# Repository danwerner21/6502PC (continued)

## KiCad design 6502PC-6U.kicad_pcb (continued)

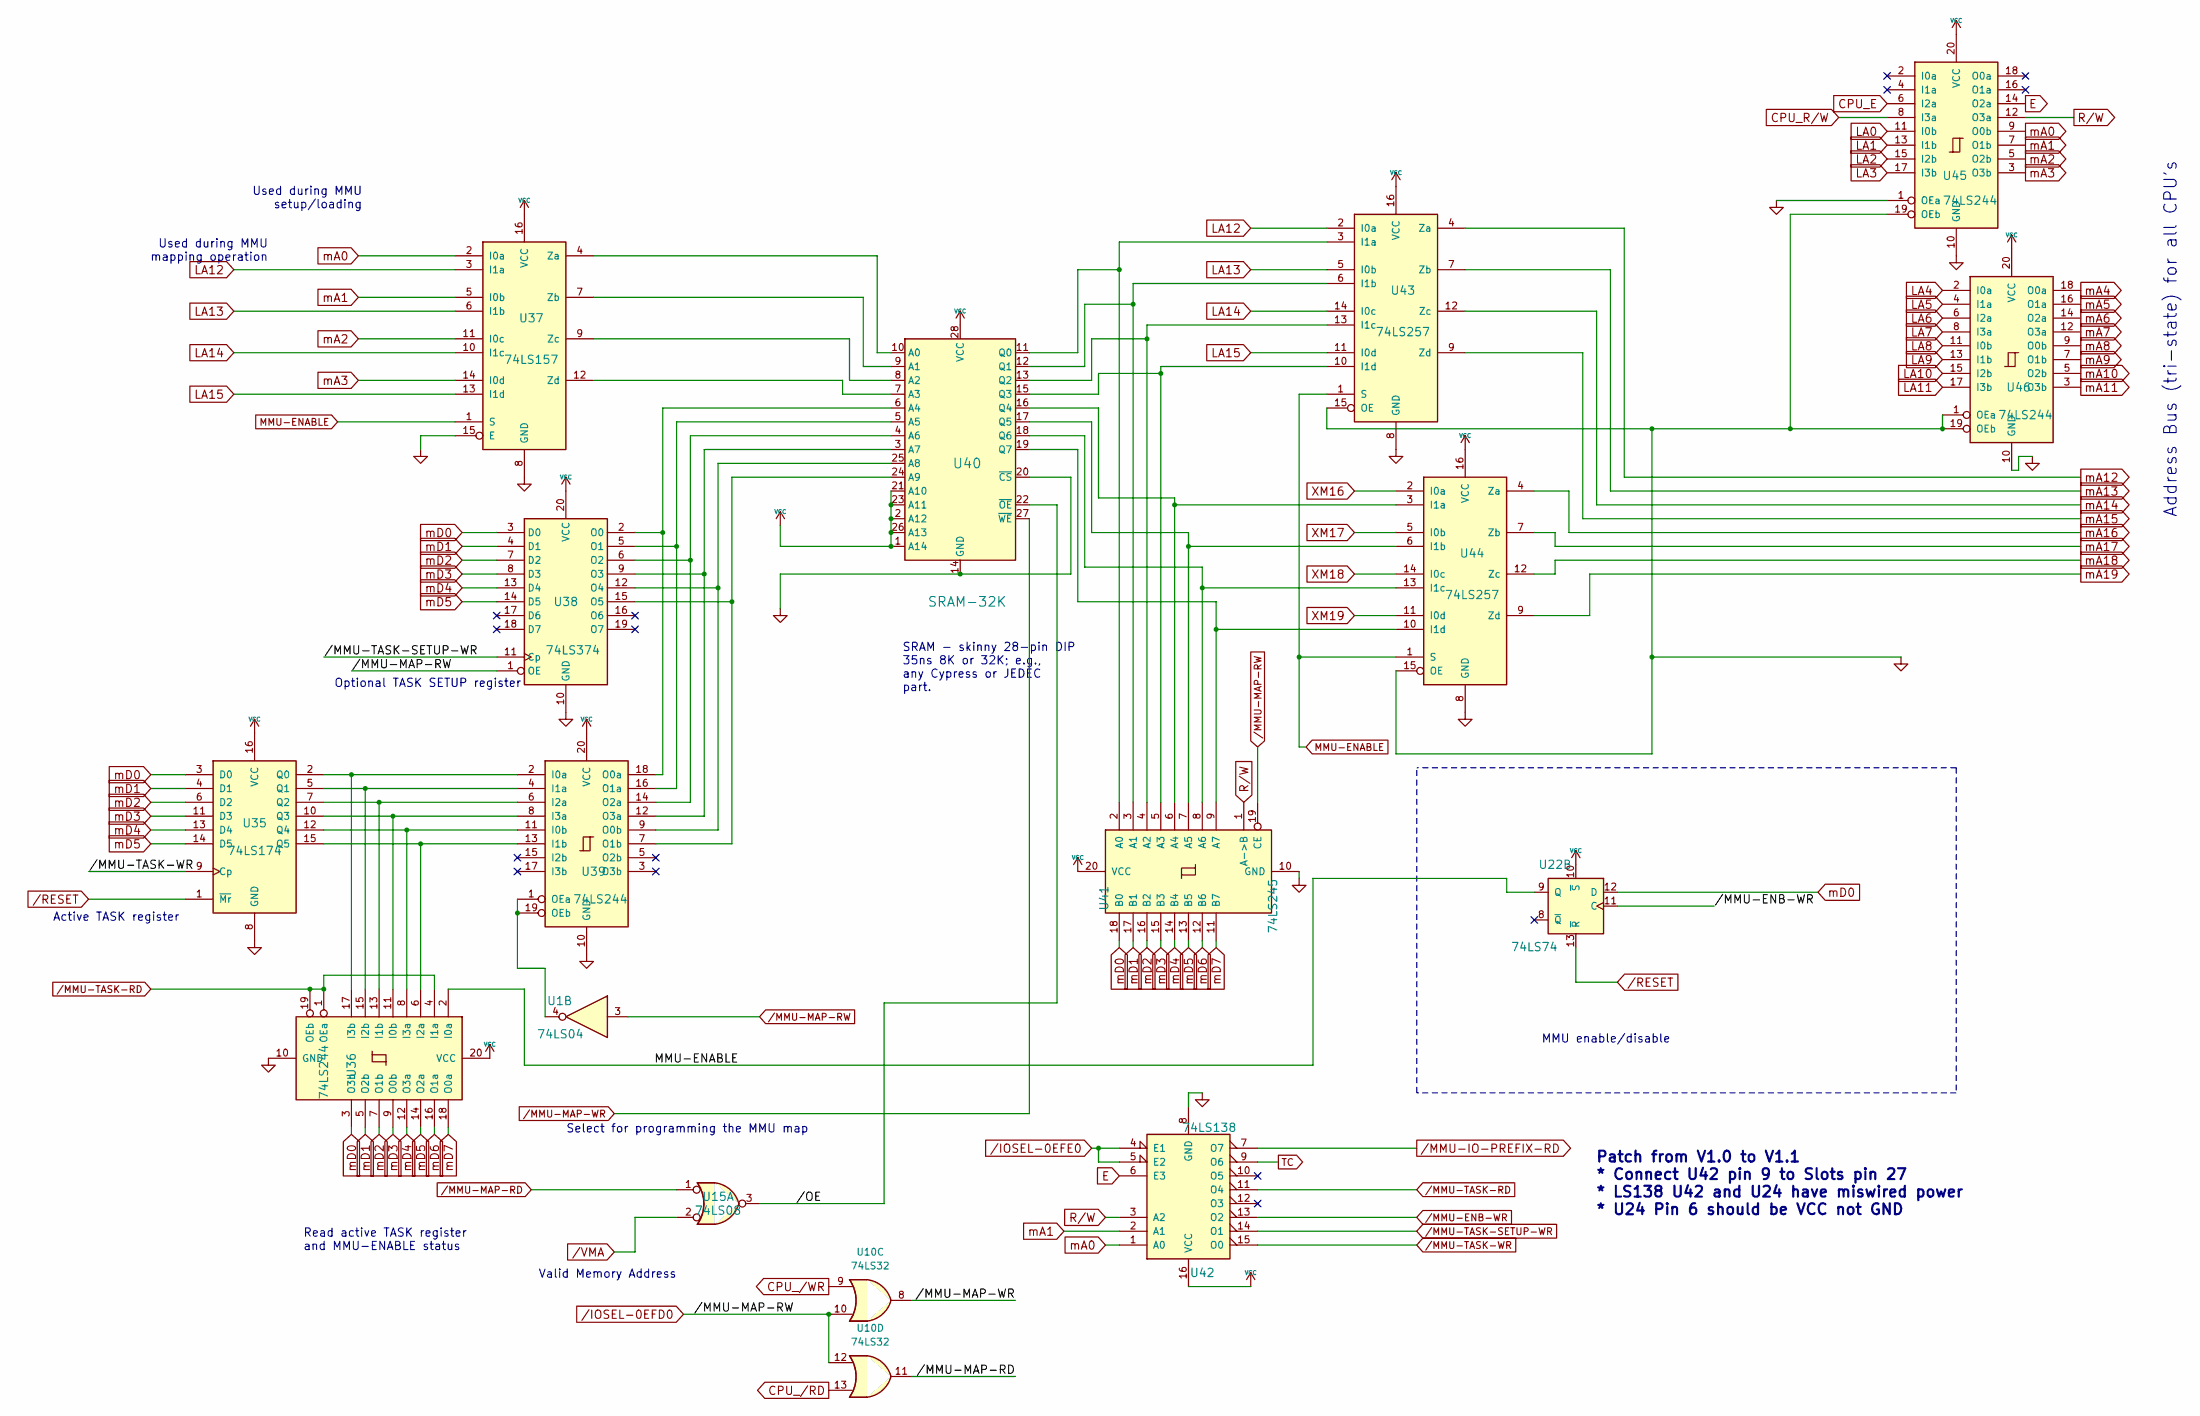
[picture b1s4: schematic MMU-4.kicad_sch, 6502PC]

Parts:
U1: 74LS04; STD_DDW_DIP14
U10: 74LS32; STD_DDW_DIP14
U15: 74LS08; STD_DDW_DIP14
U22: 74LS74; STD_DDW_DIP14
U35: 74LS174; STD_DDW_DIP16
U36, U39, U45, U46: 74LS244; STD_DDW_DIP20
U37: 74LS157; STD_DDW_DIP16
U38: 74LS374; STD_DDW_DIP20
U40: SRAM-32K; STD_DDW_DIP28_SKINNY
U41: 74LS245; STD_DDW_DIP20
U42: 74LS138; STD_DDW_DIP16
U43, U44: 74LS257; STD_DDW_DIP16

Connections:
+5V: U22.10 (~S), U35.16 (VCC), U36.20 (VCC), U37.16 (VCC), U38.20 (VCC), U39.20 (VCC), U40.1 (A14), U40.2 (A12), U40.21 (A10), U40.23 (A11), U40.26 (A13), U40.28 (VCC), U41.20 (VCC), U42.16 (VCC), U43.16 (VCC), U44.16 (VCC), U45.20 (VCC), U46.20 (VCC); also elsewhere on the board
/MMU four//OE: U15.3, U40.22 (~OE)
CPU_E: U45.6 (I2a); also elsewhere on the board
CPU_R/W: U45.8 (I3a); also elsewhere on the board
CPU_/RD: U10.13; also elsewhere on the board
CPU_/WR: U10.9; also elsewhere on the board
E: U42.6 (E3), U45.14 (O2a); also elsewhere on the board
GND: U35.8 (GND), U36.10 (GND), U37.8 (GND), U37.15 (E), U38.10 (GND), U39.10 (GND), U40.14 (GND), U40.20 (~CS), U41.10 (GND), U42.8 (GND), U43.8 (GND), U43.15 (OE), U44.8 (GND), U44.15 (OE), U45.1 (OEa), U45.10 (GND), U45.19 (OEb), U46.1 (OEa), U46.10 (GND), U46.19 (OEb); also elsewhere on the board
LA0: U45.11 (I0b); also elsewhere on the board
LA1: U45.13 (I1b); also elsewhere on the board
LA2: U45.15 (I2b); also elsewhere on the board
LA3: U45.17 (I3b); also elsewhere on the board
LA4: U46.2 (I0a); also elsewhere on the board
LA5: U46.4 (I1a); also elsewhere on the board
LA6: U46.6 (I2a); also elsewhere on the board
LA7: U46.8 (I3a); also elsewhere on the board
LA8: U46.11 (I0b); also elsewhere on the board
LA9: U46.13 (I1b); also elsewhere on the board
LA10: U46.15 (I2b); also elsewhere on the board
LA11: U46.17 (I3b); also elsewhere on the board
LA12: U37.3 (I1a), U43.2 (I0a); also elsewhere on the board
LA13: U37.6 (I1b), U43.5 (I0b); also elsewhere on the board
LA14: U37.10 (I1c), U43.14 (I0c); also elsewhere on the board
LA15: U37.13 (I1d), U43.11 (I0d); also elsewhere on the board
MMU-ENABLE: U22.9 (Q), U36.2 (I0a), U37.1 (S), U43.1 (S), U44.1 (S)
unnamed: U35.2 (Q0), U36.17 (I3b), U39.2 (I0a)
unnamed: U35.5 (Q1), U36.15 (I2b), U39.4 (I1a)
unnamed: U35.7 (Q2), U36.13 (I1b), U39.6 (I2a)
unnamed: U35.10 (Q3), U36.11 (I0b), U39.8 (I3a)
unnamed: U35.12 (Q4), U36.8 (I3a), U39.11 (I0b)
unnamed: U35.15 (Q5), U36.6 (I2a), U39.13 (I1b)
unnamed: U37.4 (Za), U40.10 (A0)
unnamed: U37.7 (Zb), U40.9 (A1)
unnamed: U37.9 (Zc), U40.8 (A2)
unnamed: U37.12 (Zd), U40.7 (A3)
unnamed: U38.2 (O0), U39.18 (O0a), U40.6 (A4)
unnamed: U38.5 (O1), U39.16 (O1a), U40.5 (A5)
unnamed: U38.6 (O2), U39.14 (O2a), U40.4 (A6)
unnamed: U38.9 (O3), U39.12 (O3a), U40.3 (A7)
unnamed: U38.12 (O4), U39.9 (O0b), U40.25 (A8)
unnamed: U38.15 (O5), U39.7 (O1b), U40.24 (A9)
unnamed: U1.4, U39.1 (OEa), U39.19 (OEb)
unnamed: U40.11 (Q0), U41.2 (A0), U43.3 (I1a)
unnamed: U40.12 (Q1), U41.3 (A1), U43.6 (I1b)
unnamed: U40.13 (Q2), U41.4 (A2), U43.13 (I1c)
unnamed: U40.15 (Q3), U41.5 (A3), U43.10 (I1d)
unnamed: U40.16 (Q4), U41.6 (A4), U44.3 (I1a)
unnamed: U40.17 (Q5), U41.7 (A5), U44.6 (I1b)
unnamed: U40.18 (Q6), U41.8 (A6), U44.13 (I1c)
unnamed: U40.19 (Q7), U41.9 (A7), U44.10 (I1d)
R/W: U41.1 (A->B), U42.3 (A2), U45.12 (O3a); also elsewhere on the board
TC: U42.9 (O6); also elsewhere on the board
XM16: U44.2 (I0a); also elsewhere on the board
XM17: U44.5 (I0b); also elsewhere on the board
XM18: U44.14 (I0c); also elsewhere on the board
XM19: U44.11 (I0d); also elsewhere on the board
mA0: U37.2 (I0a), U42.1 (A0), U45.9 (O0b); also elsewhere on the board
mA1: U37.5 (I0b), U42.2 (A1), U45.7 (O1b); also elsewhere on the board
mA2: U37.11 (I0c), U45.5 (O2b); also elsewhere on the board
mA3: U37.14 (I0d), U45.3 (O3b); also elsewhere on the board
mA4: U46.18 (O0a); also elsewhere on the board
mA5: U46.16 (O1a); also elsewhere on the board
mA6: U46.14 (O2a); also elsewhere on the board
mA7: U46.12 (O3a); also elsewhere on the board
mA8: U46.9 (O0b); also elsewhere on the board
mA9: U46.7 (O1b); also elsewhere on the board
mA10: U46.5 (O2b); also elsewhere on the board
mA11: U46.3 (O3b); also elsewhere on the board
mA12: U43.4 (Za); also elsewhere on the board
mA13: U43.7 (Zb); also elsewhere on the board
mA14: U43.12 (Zc); also elsewhere on the board
mA15: U43.9 (Zd); also elsewhere on the board
mA16: U44.4 (Za); also elsewhere on the board
mA17: U44.7 (Zb); also elsewhere on the board
mA18: U44.12 (Zc); also elsewhere on the board
mA19: U44.9 (Zd); also elsewhere on the board
mD0: U22.12 (D), U35.3 (D0), U36.3 (O3b), U38.3 (D0), U41.18 (B0); also elsewhere on the board
mD1: U35.4 (D1), U36.5 (O2b), U38.4 (D1), U41.17 (B1); also elsewhere on the board
mD2: U35.6 (D2), U36.7 (O1b), U38.7 (D2), U41.16 (B2); also elsewhere on the board
mD3: U35.11 (D3), U36.9 (O0b), U38.8 (D3), U41.15 (B3); also elsewhere on the board
mD4: U35.13 (D4), U36.12 (O3a), U38.13 (D4), U41.14 (B4); also elsewhere on the board
mD5: U35.14 (D5), U36.14 (O2a), U38.14 (D5), U41.13 (B5); also elsewhere on the board
mD6: U36.16 (O1a), U41.12 (B6); also elsewhere on the board
mD7: U36.18 (O0a), U41.11 (B7); also elsewhere on the board
/IOSEL-0EFE0: U42.4 (E1), U42.5 (E2); also elsewhere on the board
/MMU-IO-PREFIX-RD: U42.7 (O7); also elsewhere on the board
/MMU-TASK-RD: U36.1 (OEa), U36.4 (I1a), U36.19 (OEb), U42.11 (O4)
/VMA: U15.2; also elsewhere on the board

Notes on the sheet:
MMU enable/disable
Address Bus (tri-state) for all CPU's
Read active TASK register and MMU-ENABLE status
Optional TASK SETUP register
Active TASK register
Select for programming the MMU map
Used during MMU setup/loading
Valid Memory Address
Patch from V1.0 to V1.1 * Connect U42 pin 9 to Slots pin 27 * LS138 U42 and U24 have miswired power * U24 Pin 6 should be VCC not GND
SRAM - skinny 28-pin DIP 35ns 8K or 32K; e.g., any Cypress or JEDEC part.
Used during MMU mapping operation

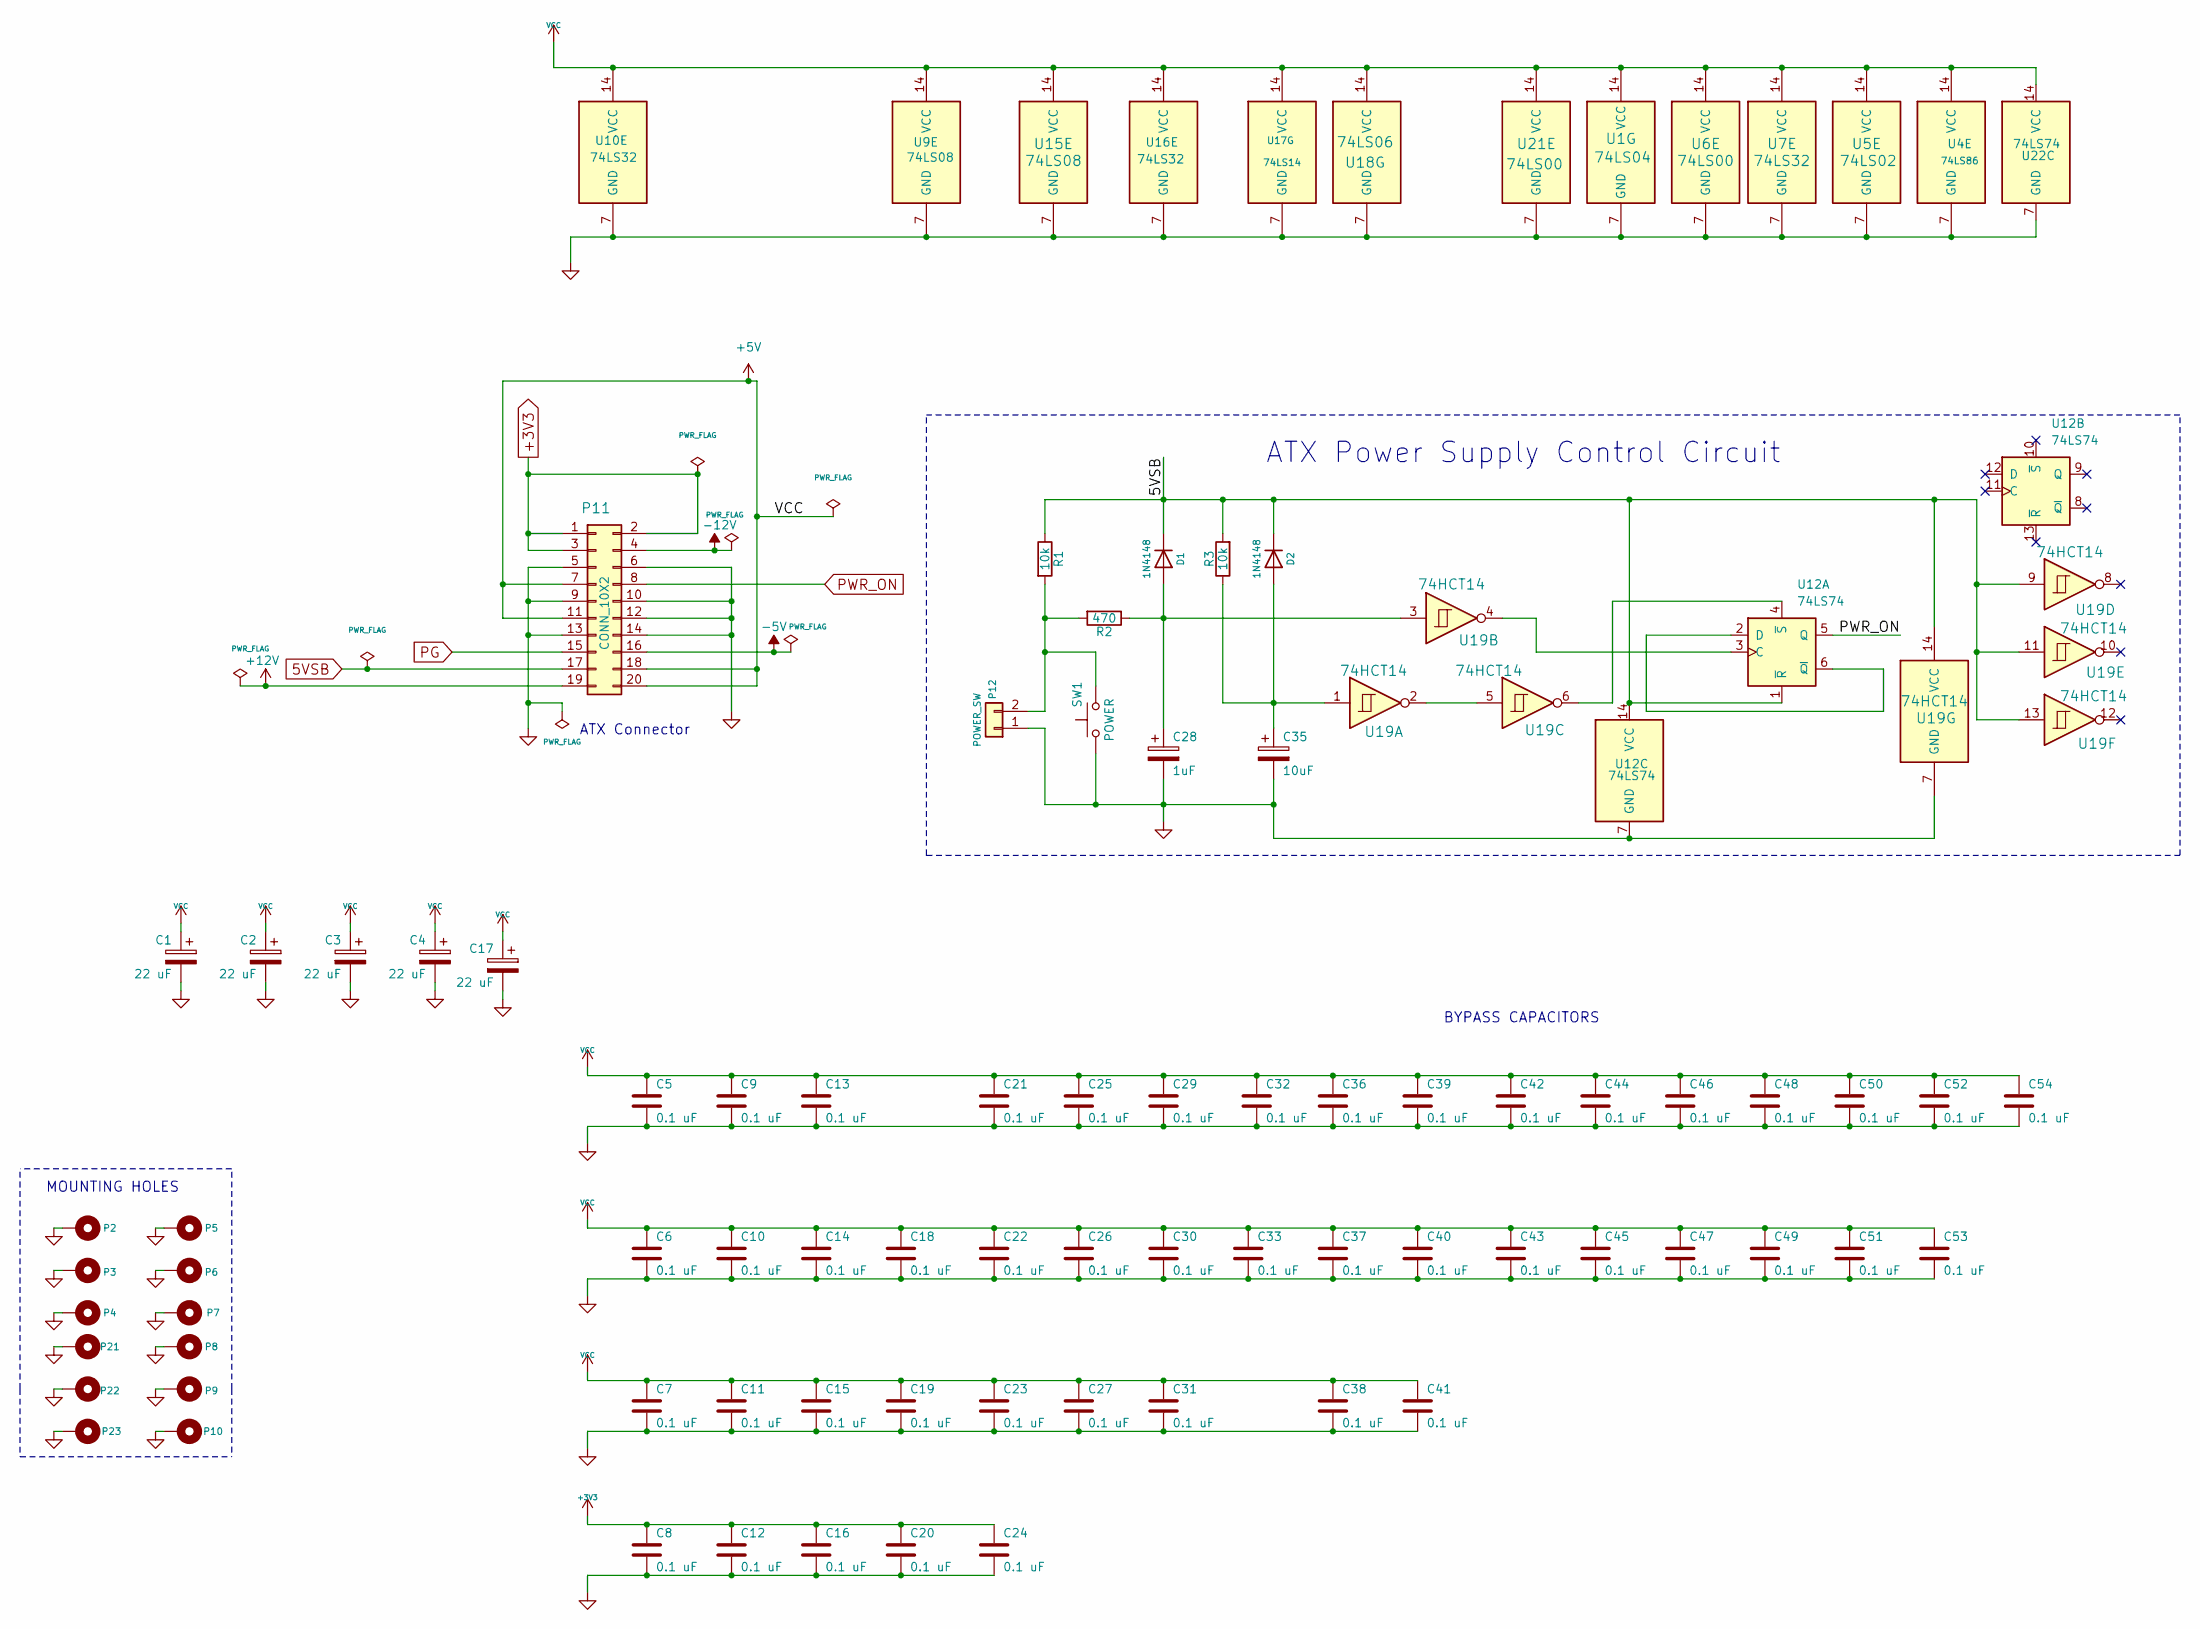
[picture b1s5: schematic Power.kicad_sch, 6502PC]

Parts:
C1, C2, C3, C4, C17: 22 uF; STD_DDW_PCAP
C5, C6, C7, C8, C9, C10, C11, C12, C13, C14, C15, C16, C18, C19, C20, C21, C22, C23, C24, C25, C26, C27, C29, C30, C31, C32, C33, C36, C37, C38, C39, C40, C41, C42, C43, C44, C45, C46, C47, C48, C49, C50, C51, C52, C53, C54: 0.1 uF; STD_DDW_CAP
C28: 1uF; STD_DDW_PCAP
C35: 10uF; STD_DDW_PCAP
D1, D2: 1N4148; STD_DDW_DIODE
P2, P3, P4, P5, P6, P7, P8, P9, P10, P21, P22, P23: CONN_1; MountingHole_3.2mm_M3_Pad_TopBottom
P11: CONN_10X2; ATXConnector
P12: POWER_SW; STD_DDW_PINHEAD_V_1x02
R1, R3: 10k; STD_DDW_RESISTOR
R2: 470; STD_DDW_RESISTOR
SW1: POWER; STD_DDW_TACTSW
U1: 74LS04; STD_DDW_DIP14
U4: 74LS86; STD_DDW_DIP14
U5: 74LS02; STD_DDW_DIP14
U6, U21: 74LS00; STD_DDW_DIP14
U7, U10, U16: 74LS32; STD_DDW_DIP14
U9, U15: 74LS08; STD_DDW_DIP14
U12, U22: 74LS74; STD_DDW_DIP14
U17: 74LS14; STD_DDW_DIP14
U18: 74LS06; STD_DDW_DIP14
U19: 74HCT14; STD_DDW_DIP14

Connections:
5VSB: D1.1 (K), D2.1 (K), P11.17, R1.1, R3.2, U12.1 (~R), U12.14 (VCC), U19.9, U19.11, U19.13, U19.14 (VCC)
+3V3: C8.1, C12.1, C16.1, C20.1, C24.1, P11.1, P11.2, P11.3
+5V: C1.1, C2.1, C3.1, C4.1, C5.1, C6.1, C7.1, C9.1, C10.1, C11.1, C13.1, C14.1, C15.1, C17.1, C18.1, C19.1, C21.1, C22.1, C23.1, C25.1, C26.1, C27.1, C29.1, C30.1, C31.1, C32.1, C33.1, C36.1, C37.1, C38.1, C39.1, C40.1, C41.1, C42.1, C43.1, C44.1, C45.1, C46.1, C47.1, C48.1, C49.1, C50.1, C51.1, C52.1, C53.1, C54.1, P11.7, P11.11, P11.18, P11.20, U1.14 (VCC), U4.14 (VCC), U5.14 (VCC), U6.14 (VCC), U7.14 (VCC), U9.14 (VCC), U10.14 (VCC), U15.14 (VCC), U16.14 (VCC), U17.14 (VCC), U18.14 (VCC), U21.14 (VCC), U22.14 (VCC); also elsewhere on the board
+12V: P11.19; also elsewhere on the board
-5V: P11.16; also elsewhere on the board
-12V: P11.4; also elsewhere on the board
GND: C1.2, C2.2, C3.2, C4.2, C5.2, C6.2, C7.2, C8.2, C9.2, C10.2, C11.2, C12.2, C13.2, C14.2, C15.2, C16.2, C17.2, C18.2, C19.2, C20.2, C21.2, C22.2, C23.2, C24.2, C25.2, C26.2, C27.2, C28.2, C29.2, C30.2, C31.2, C32.2, C33.2, C35.2, C36.2, C37.2, C38.2, C39.2, C40.2, C41.2, C42.2, C43.2, C44.2, C45.2, C46.2, C47.2, C48.2, C49.2, C50.2, C51.2, C52.2, C53.2, C54.2, P2.1, P3.1, P4.1, P5.1, P6.1, P7.1, P8.1, P9.1, P10.1, P11.5, P11.6, P11.9, P11.10, P11.12, P11.13, P11.14, P12.1, P21.1, P22.1, P23.1, SW1.1, U1.7 (GND), U4.7 (GND), U5.7 (GND), U6.7 (GND), U7.7 (GND), U9.7 (GND), U10.7 (GND), U12.7 (GND), U15.7 (GND), U16.7 (GND), U17.7 (GND), U18.7 (GND), U19.7 (GND), U21.7 (GND), U22.7 (GND); also elsewhere on the board
unnamed: C28.1, D1.2 (A), R2.1, U19.3
unnamed: C35.1, D2.2 (A), R3.1, U19.1
unnamed: P12.2, R1.2, R2.2, SW1.2
unnamed: U12.3 (C), U19.4
unnamed: U12.2 (D), U12.6 (~Q)
unnamed: U12.4 (~S), U19.6
unnamed: U19.2, U19.5
PG: P11.15; also elsewhere on the board
PWR_ON: P11.8, U12.5 (Q)

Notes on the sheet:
BYPASS CAPACITORS
MOUNTING HOLES
ATX Connector
ATX Power Supply Control Circuit

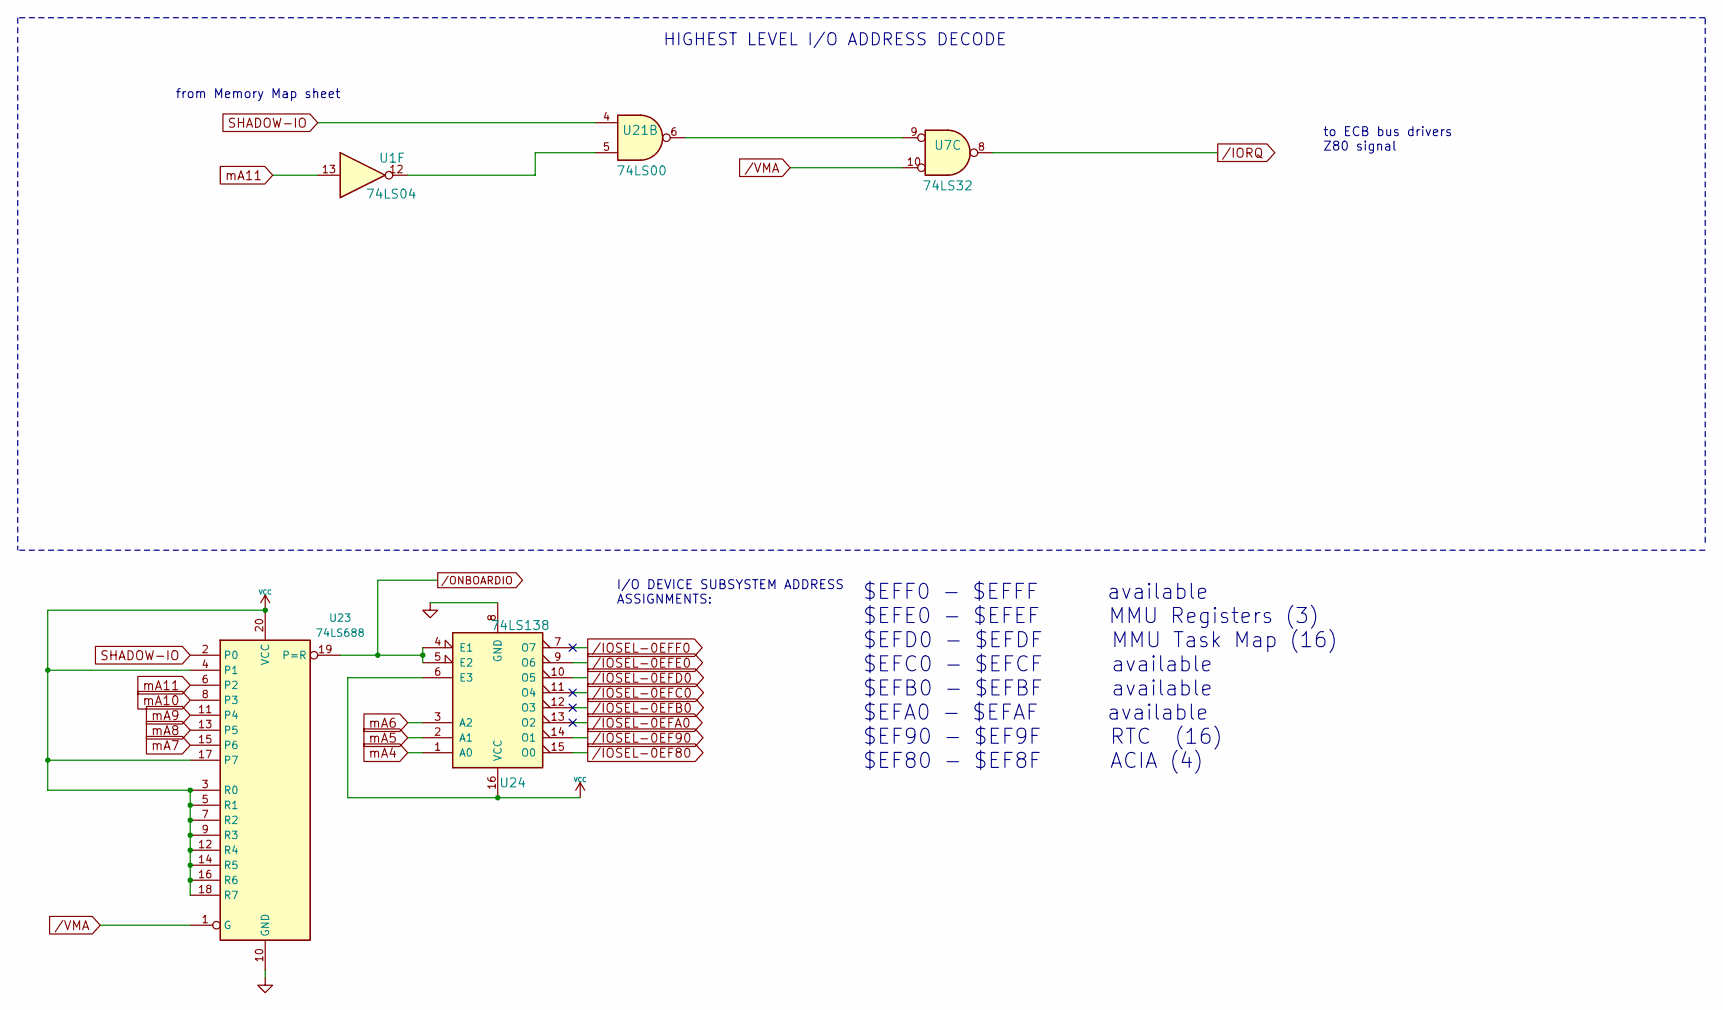
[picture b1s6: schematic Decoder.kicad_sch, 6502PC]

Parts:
U1: 74LS04; STD_DDW_DIP14
U7: 74LS32; STD_DDW_DIP14
U21: 74LS00; STD_DDW_DIP14
U23: 74LS688; STD_DDW_DIP20
U24: 74LS138; STD_DDW_DIP16

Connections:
+5V: U23.3 (R0), U23.4 (P1), U23.5 (R1), U23.7 (R2), U23.9 (R3), U23.12 (R4), U23.14 (R5), U23.16 (R6), U23.17 (P7), U23.18 (R7), U23.20 (VCC), U24.6 (E3), U24.16 (VCC); also elsewhere on the board
GND: U23.10 (GND), U24.8 (GND); also elsewhere on the board
unnamed: U1.12, U21.5
unnamed: U7.9, U21.6
SHADOW-IO: U21.4, U23.2 (P0); also elsewhere on the board
mA4: U24.1 (A0); also elsewhere on the board
mA5: U24.2 (A1); also elsewhere on the board
mA6: U24.3 (A2); also elsewhere on the board
mA7: U23.15 (P6); also elsewhere on the board
mA8: U23.13 (P5); also elsewhere on the board
mA9: U23.11 (P4); also elsewhere on the board
mA10: U23.8 (P3); also elsewhere on the board
mA11: U1.13, U23.6 (P2); also elsewhere on the board
/IOSEL-0EF80: U24.15 (O0); also elsewhere on the board
/IOSEL-0EF90: U24.14 (O1); also elsewhere on the board
/IOSEL-0EFA0: U24.13 (O2)
/IOSEL-0EFB0: U24.12 (O3)
/IOSEL-0EFC0: U24.11 (O4)
/IOSEL-0EFE0: U24.9 (O6); also elsewhere on the board
/IOSEL-0EFF0: U24.7 (O7)
/ONBOARDIO: U23.19 (P=R), U24.4 (E1), U24.5 (E2); also elsewhere on the board
/VMA: U7.10, U23.1 (G); also elsewhere on the board

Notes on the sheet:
to ECB bus drivers Z80 signal
HIGHEST LEVEL I/O ADDRESS DECODE
$EFF0 - $EFFF available $EFE0 - $EFEF MMU Registers (3) $EFD0 - $EFDF MMU Task Map (16) $EFC0 - $EFCF available $EFB0 - $EFBF available $EFA0 - $EFAF available $EF90 - $EF9F RTC (16) $EF80 - $EF8F ACIA (4)
from Memory Map sheet
I/O DEVICE SUBSYSTEM ADDRESS ASSIGNMENTS:

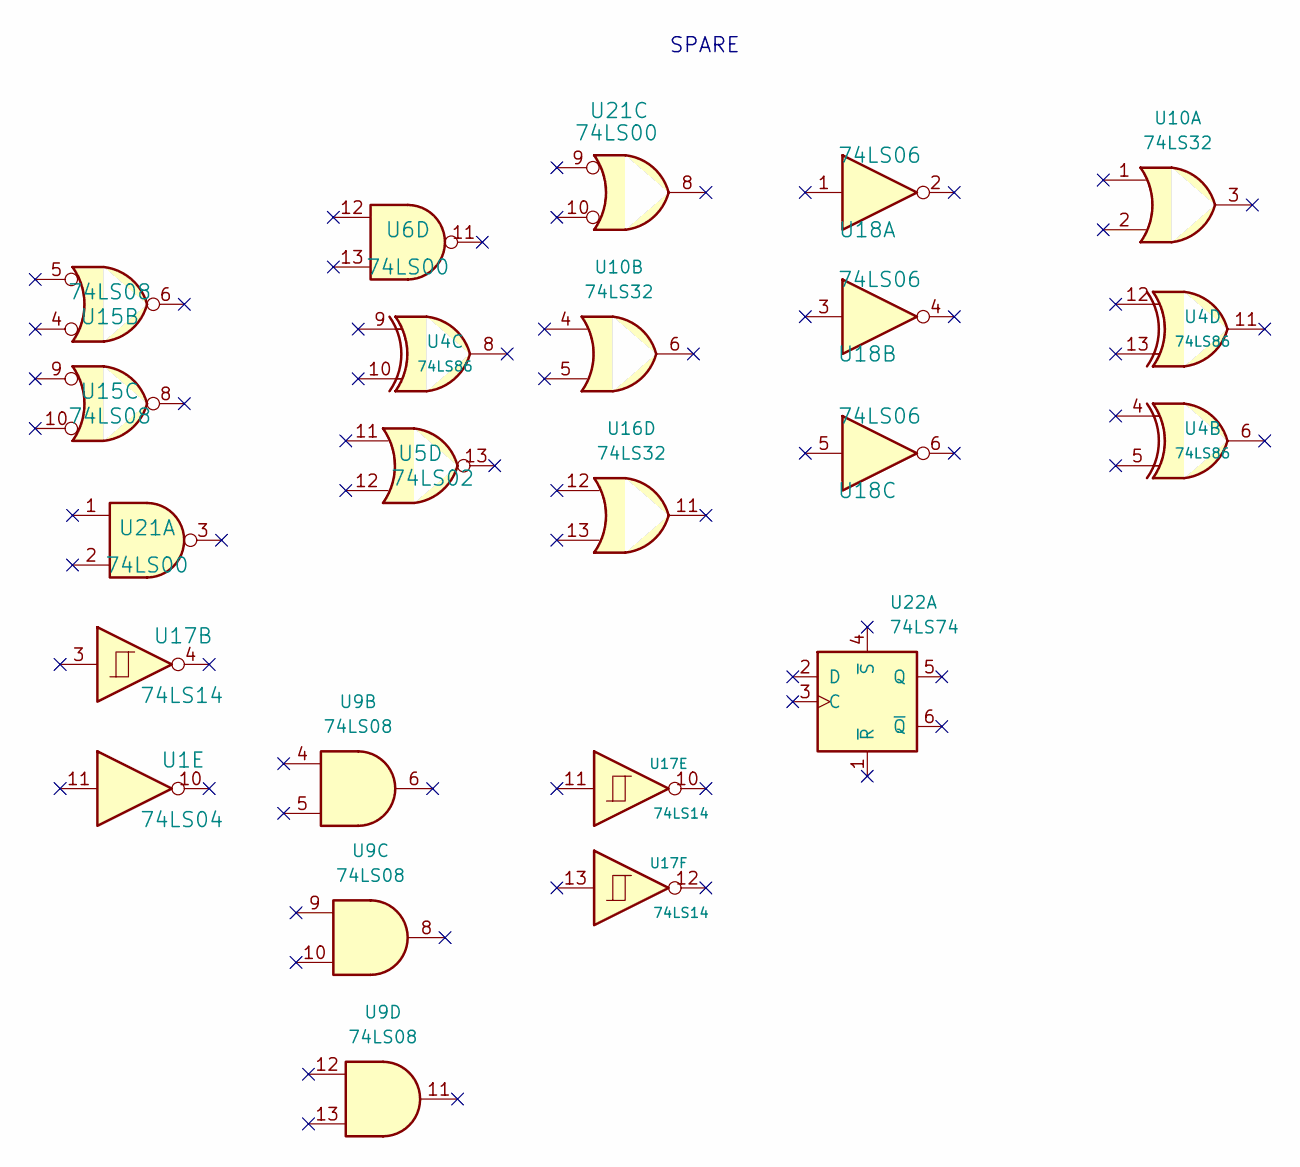
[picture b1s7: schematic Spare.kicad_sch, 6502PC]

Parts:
U1: 74LS04; STD_DDW_DIP14
U4: 74LS86; STD_DDW_DIP14
U5: 74LS02; STD_DDW_DIP14
U6, U21: 74LS00; STD_DDW_DIP14
U9, U15: 74LS08; STD_DDW_DIP14
U10, U16: 74LS32; STD_DDW_DIP14
U17: 74LS14; STD_DDW_DIP14
U18: 74LS06; STD_DDW_DIP14
U22: 74LS74; STD_DDW_DIP14

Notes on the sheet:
SPARE

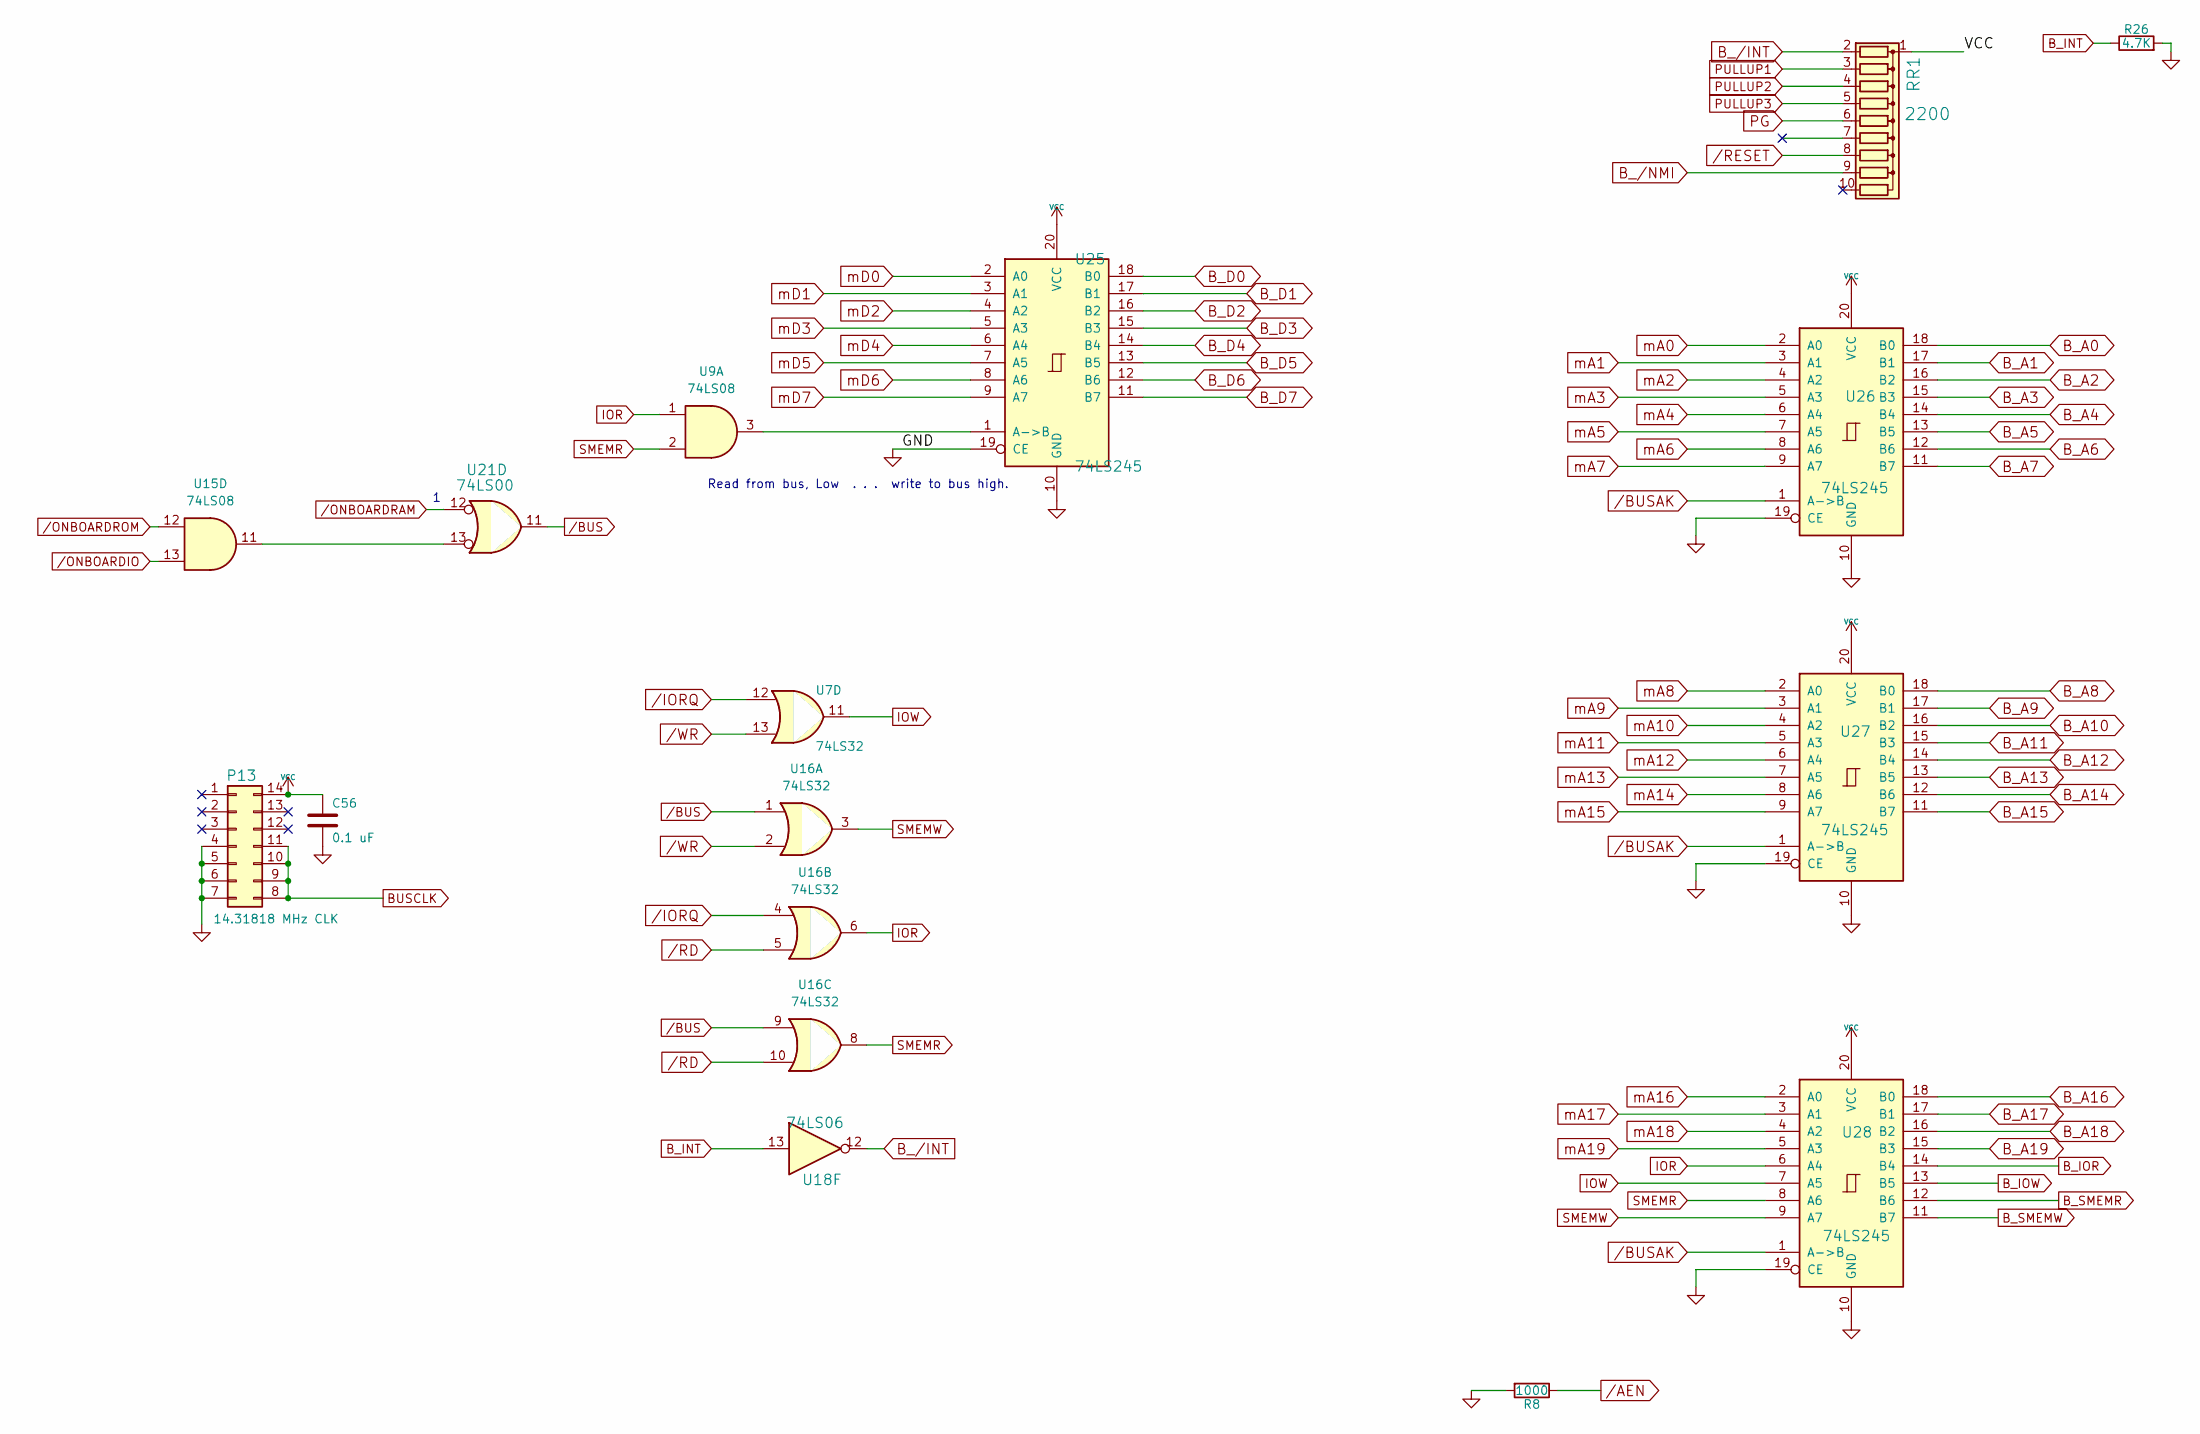
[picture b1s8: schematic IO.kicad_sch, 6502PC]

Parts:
C56: 0.1 uF; STD_DDW_CAP
P13: 14.31818 MHz CLK; STD_DDW_DIP14
R8: 1000; STD_DDW_RESISTOR
R26: 4.7K; STD_DDW_RESISTOR
RR1: 2200; STD_DDW_SIP10
U7, U16: 74LS32; STD_DDW_DIP14
U9, U15: 74LS08; STD_DDW_DIP14
U18: 74LS06; STD_DDW_DIP14
U21: 74LS00; STD_DDW_DIP14
U25, U26, U27, U28: 74LS245; STD_DDW_DIP20

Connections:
+5V: C56.1, P13.14, RR1.1 (common), U25.20 (VCC), U26.20 (VCC), U27.20 (VCC), U28.20 (VCC); also elsewhere on the board
BUSCLK: P13.8, P13.9, P13.10, P13.11; also elsewhere on the board
B_A0: U26.18 (B0); also elsewhere on the board
B_A1: U26.17 (B1); also elsewhere on the board
B_A2: U26.16 (B2); also elsewhere on the board
B_A3: U26.15 (B3); also elsewhere on the board
B_A4: U26.14 (B4); also elsewhere on the board
B_A5: U26.13 (B5); also elsewhere on the board
B_A6: U26.12 (B6); also elsewhere on the board
B_A7: U26.11 (B7); also elsewhere on the board
B_A8: U27.18 (B0); also elsewhere on the board
B_A9: U27.17 (B1); also elsewhere on the board
B_A10: U27.16 (B2); also elsewhere on the board
B_A11: U27.15 (B3); also elsewhere on the board
B_A12: U27.14 (B4); also elsewhere on the board
B_A13: U27.13 (B5); also elsewhere on the board
B_A14: U27.12 (B6); also elsewhere on the board
B_A15: U27.11 (B7); also elsewhere on the board
B_A16: U28.18 (B0); also elsewhere on the board
B_A17: U28.17 (B1); also elsewhere on the board
B_A18: U28.16 (B2); also elsewhere on the board
B_A19: U28.15 (B3); also elsewhere on the board
B_D0: U25.18 (B0); also elsewhere on the board
B_D1: U25.17 (B1); also elsewhere on the board
B_D2: U25.16 (B2); also elsewhere on the board
B_D3: U25.15 (B3); also elsewhere on the board
B_D4: U25.14 (B4); also elsewhere on the board
B_D5: U25.13 (B5); also elsewhere on the board
B_D6: U25.12 (B6); also elsewhere on the board
B_D7: U25.11 (B7); also elsewhere on the board
B_INT: R26.1, U18.13; also elsewhere on the board
B_IOR: U28.14 (B4); also elsewhere on the board
B_IOW: U28.13 (B5); also elsewhere on the board
B_SMEMR: U28.12 (B6); also elsewhere on the board
B_SMEMW: U28.11 (B7); also elsewhere on the board
B_/INT: RR1.2 (R1), U18.12; also elsewhere on the board
B_/NMI: RR1.9 (R8); also elsewhere on the board
GND: C56.2, P13.4, P13.5, P13.6, P13.7, R8.2, R26.2, U25.10 (GND), U25.19 (CE), U26.10 (GND), U26.19 (CE), U27.10 (GND), U27.19 (CE), U28.10 (GND), U28.19 (CE); also elsewhere on the board
IOR: U9.1, U16.6, U28.6 (A4)
IOW: U7.11, U28.7 (A5)
unnamed: U15.11, U21.13
unnamed: U9.3, U25.1 (A->B)
PG: RR1.6 (R5); also elsewhere on the board
PULLUP1: RR1.3 (R2); also elsewhere on the board
PULLUP2: RR1.4 (R3); also elsewhere on the board
PULLUP3: RR1.5 (R4); also elsewhere on the board
SMEMR: U9.2, U16.8, U28.8 (A6)
SMEMW: U16.3, U28.9 (A7)
mA0: U26.2 (A0); also elsewhere on the board
mA1: U26.3 (A1); also elsewhere on the board
mA2: U26.4 (A2); also elsewhere on the board
mA3: U26.5 (A3); also elsewhere on the board
mA4: U26.6 (A4); also elsewhere on the board
mA5: U26.7 (A5); also elsewhere on the board
mA6: U26.8 (A6); also elsewhere on the board
mA7: U26.9 (A7); also elsewhere on the board
mA8: U27.2 (A0); also elsewhere on the board
mA9: U27.3 (A1); also elsewhere on the board
mA10: U27.4 (A2); also elsewhere on the board
mA11: U27.5 (A3); also elsewhere on the board
mA12: U27.6 (A4); also elsewhere on the board
mA13: U27.7 (A5); also elsewhere on the board
mA14: U27.8 (A6); also elsewhere on the board
mA15: U27.9 (A7); also elsewhere on the board
mA16: U28.2 (A0); also elsewhere on the board
mA17: U28.3 (A1); also elsewhere on the board
mA18: U28.4 (A2); also elsewhere on the board
mA19: U28.5 (A3); also elsewhere on the board
mD0: U25.2 (A0); also elsewhere on the board
mD1: U25.3 (A1); also elsewhere on the board
mD2: U25.4 (A2); also elsewhere on the board
mD3: U25.5 (A3); also elsewhere on the board
mD4: U25.6 (A4); also elsewhere on the board
mD5: U25.7 (A5); also elsewhere on the board
mD6: U25.8 (A6); also elsewhere on the board
mD7: U25.9 (A7); also elsewhere on the board
/AEN: R8.1; also elsewhere on the board
/BUS: U16.1, U16.9, U21.11
/BUSAK: U26.1 (A->B), U27.1 (A->B), U28.1 (A->B); also elsewhere on the board
/ONBOARDIO: U15.13; also elsewhere on the board
/ONBOARDRAM: U21.12; also elsewhere on the board
/ONBOARDROM: U15.12; also elsewhere on the board
/RD: U16.5, U16.10; also elsewhere on the board
/WR: U7.13, U16.2; also elsewhere on the board

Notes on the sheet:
Read from bus, Low . . . write to bus high.

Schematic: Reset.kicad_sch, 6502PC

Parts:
C57: 0.01 uF; STD_DDW_CAP
JP1: JUMPER; STD_DDW_PINHEAD_V_1x02
SW2: RESET; STD_DDW_TACTSW
U17: 74LS14; STD_DDW_DIP14
U29: DS1233; STD_DDW_TO92

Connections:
+5V: U29.3; also elsewhere on the board
GND: C57.2, JP1.2, SW2.1, U29.1; also elsewhere on the board
RESET: U17.8; also elsewhere on the board

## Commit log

2025-10-12 PCB Routed
2025-12-21 V1.1
2025-12-28 minor schematic clean up
2025-12-28 fix rtc
2026-01-19 add photos
